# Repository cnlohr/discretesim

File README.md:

# (work in progress) Dumb as a Box of Rocks SPICE Simulation

goals:
1. as simple as possible
2. linear runtime with circuit complexity.
3. support ultra complicated circuits.
4. be stable-by-default at the trade off of simulation speed.

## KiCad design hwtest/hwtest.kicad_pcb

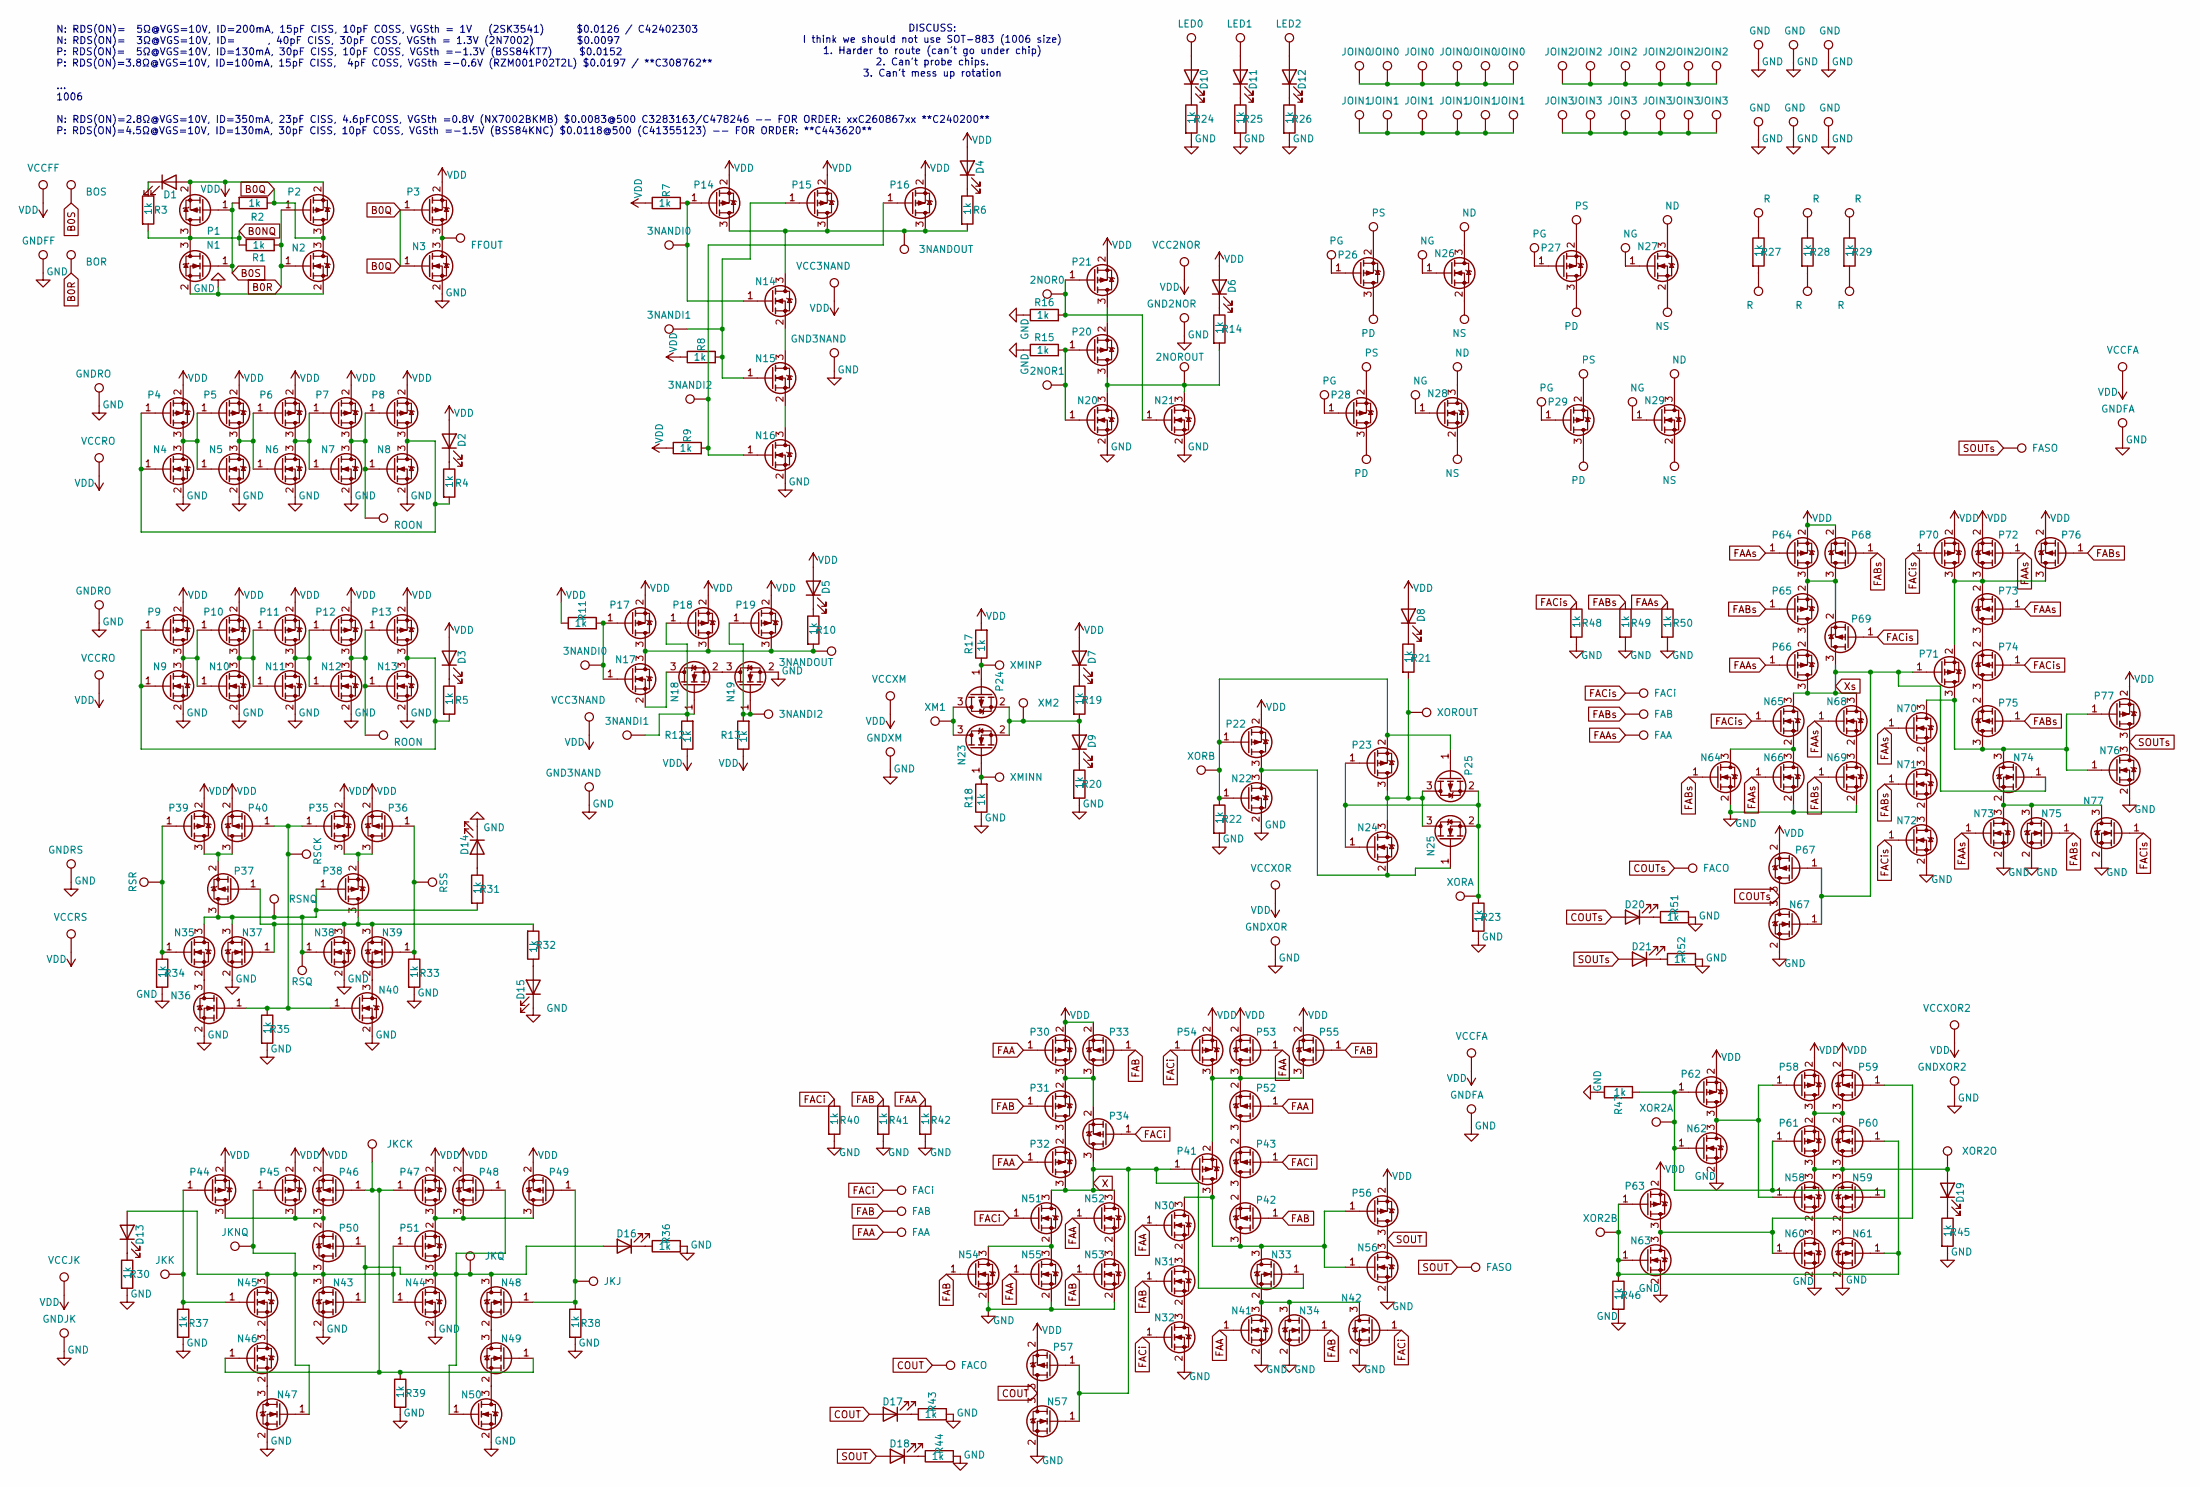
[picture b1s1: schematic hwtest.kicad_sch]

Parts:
D1, D2, D3, D4, D5, D6, D7, D8, D9, D10, D11, D12, D13, D14, D15, D16, D17, D18, D19, D20, D21: LED; LED_0402_1005Metric_COMPACT; LCSC C965793
N1, N2, N3, N4, N5, N6, N7, N8, N14, N15, N16, N20, N21, N22, N23, N24, N25, N26, N27, N30, N31, N32, N33, N34, N35, N36, N37, N38, N39, N40, N41, N42, N43, N44, N45, N46, N47, N48, N49, N50, N51, N52, N53, N54, N55, N56, N57, N58, N59, N60, N61, N62, N63: 2SK3541; SOT-723-COMPACT; LCSC C42402303
N9, N10, N11, N12, N13, N17, N18, N19, N28, N29: NX7002BKMB315; DFN1006-3-NCH; LCSC C240200
N64, N65, N66, N67, N68, N69, N70, N71, N72, N73, N74, N75, N76, N77: 2SK3541; DFN1006-3-NCH; LCSC C240200
P1, P2, P3, P4, P5, P6, P7, P8, P14, P15, P16, P20, P21, P22, P23, P24, P25, P26, P27, P30, P31, P32, P33, P34, P35, P36, P37, P38, P39, P40, P41, P42, P43, P44, P45, P46, P47, P48, P49, P50, P51, P52, P53, P54, P55, P56, P57, P58, P59, P60, P61, P62, P63: RZM001P02T2L; SOT-723-COMPACTP; LCSC C308762
P9, P10, P11, P12, P13, P17, P18, P19, P28, P29: BSS84KNC; DFN1006-3-PCH; LCSC C443620
P64, P65, P66, P67, P68, P69, P70, P71, P72, P73, P74, P75, P76, P77: RZM001P02T2L; DFN1006-3-PCH; LCSC C443620
R1, R2, R3, R4, R5, R6, R7, R8, R9, R10, R11, R12, R13, R14, R15, R16, R17, R18, R19, R20, R21, R22, R23, R24, R25, R26, R27, R28, R29, R30, R31, R32, R33, R34, R35, R36, R37, R38, R39, R40, R41, R42, R43, R44, R45, R46, R47, R48, R49, R50, R51, R52: 1k; R_0402_1005Metric_COMPACT; LCSC C11702
TP1: BOS; TPTHRU; LCSC C25503131
TP2: BOR; TPTHRU; LCSC C25503131
TP3: FFOUT; TPTHRU; LCSC C25503131
TP4, TP11: ROON; TPTHRU; LCSC C25503131
TP5: VCCFF; TPTHRU; LCSC C25503131
TP6: GNDFF; TPTHRU; LCSC C25503131
TP7, TP9: GNDRO; TPTHRU; LCSC C25503131
TP8, TP10: VCCRO; TPTHRU; LCSC C25503131
TP12, TP21: 3NANDOUT; TPTHRU; LCSC C25503131
TP13, TP19: 3NANDI0; TPTHRU; LCSC C25503131
TP14, TP18: 3NANDI1; TPTHRU; LCSC C25503131
TP15, TP20: 3NANDI2; TPTHRU; LCSC C25503131
TP16, TP22: VCC3NAND; TPTHRU; LCSC C25503131
TP17, TP23: GND3NAND; TPTHRU; LCSC C25503131
TP24: 2NOR1; TPTHRU; LCSC C25503131
TP25: 2NOR0; TPTHRU; LCSC C25503131
TP26: 2NOROUT; TPTHRU; LCSC C25503131
TP27: VCC2NOR; TPTHRU; LCSC C25503131
TP28: GND2NOR; TPTHRU; LCSC C25503131
TP29: XORB; TPTHRU; LCSC C25503131
TP30: XM1; TPTHRU; LCSC C25503131
TP31: XM2; TPTHRU; LCSC C25503131
TP32: XMINP; TPTHRU; LCSC C25503131
TP33: XMINN; TPTHRU; LCSC C25503131
TP34: XORA; TPTHRU; LCSC C25503131
TP35: VCCXM; TPTHRU; LCSC C25503131
TP36: GNDXM; TPTHRU; LCSC C25503131
TP37: XOROUT; TPTHRU; LCSC C25503131
TP38: VCCXOR; TPTHRU; LCSC C25503131
TP39: GNDXOR; TPTHRU; LCSC C25503131
TP40: LED0; TPTHRU; LCSC C25503131
TP41: LED1; TPTHRU; LCSC C25503131
TP42: LED2; TPTHRU; LCSC C25503131
TP43, TP68, TP74, TP80: PS; TPTHRU; LCSC C25503131
TP44, TP67, TP73, TP79: PG; TPTHRU; LCSC C25503131
TP45, TP69, TP75, TP81: PD; TPTHRU; LCSC C25503131
TP46, TP71, TP77, TP83: ND; TPTHRU; LCSC C25503131
TP47, TP72, TP78, TP84: NS; TPTHRU; LCSC C25503131
TP48, TP70, TP76, TP82: NG; TPTHRU; LCSC C25503131
TP49, TP50, TP51, TP52, TP53, TP54: R; TPTHRU; LCSC C25503131
TP55, TP56, TP57, TP58, TP59, TP60: JOIN0; TPTHRU; LCSC C25503131
TP61, TP62, TP63, TP64, TP65, TP66: JOIN1; TPTHRU; LCSC C25503131
TP85, TP86, TP87, TP88, TP89, TP90: JOIN2; TPTHRU; LCSC C25503131
TP91, TP92, TP93, TP94, TP95, TP96: JOIN3; TPTHRU; LCSC C25503131
TP97, TP98, TP99, TP100, TP101, TP102: GND; TPTHRU; LCSC C25503131
TP103: JKCK; TPTHRU; LCSC C25503131
TP104: JKQ; TPTHRU; LCSC C25503131
TP105: JKNQ; TPTHRU; LCSC C25503131
TP106: RSNQ; TPTHRU; LCSC C25503131
TP107: RSQ; TPTHRU; LCSC C25503131
TP108: RSR; TPTHRU; LCSC C25503131
TP109: RSS; TPTHRU; LCSC C25503131
TP110: RSCK; TPTHRU; LCSC C25503131
TP111: GNDRS; TPTHRU; LCSC C25503131
TP112: VCCRS; TPTHRU; LCSC C25503131
TP113: JKK; TPTHRU; LCSC C25503131
TP114: JKJ; TPTHRU; LCSC C25503131
TP115: VCCJK; TPTHRU; LCSC C25503131
TP116: GNDJK; TPTHRU; LCSC C25503131
TP117, TP132: FACO; TPTHRU; LCSC C25503131
TP118, TP133: FASO; TPTHRU; LCSC C25503131
TP119, TP129: FACi; TPTHRU; LCSC C25503131
TP120, TP130: FAB; TPTHRU; LCSC C25503131
TP121, TP131: FAA; TPTHRU; LCSC C25503131
TP122, TP134: VCCFA; TPTHRU; LCSC C25503131
TP123, TP135: GNDFA; TPTHRU; LCSC C25503131
TP124: XOR2A; TPTHRU; LCSC C25503131
TP125: XOR2B; TPTHRU; LCSC C25503131
TP126: XOR2O; TPTHRU; LCSC C25503131
TP127: VCCXOR2; TPTHRU; LCSC C25503131
TP128: GNDXOR2; TPTHRU; LCSC C25503131

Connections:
B0NQ: N1.3 (D), P1.3 (D), R1.1, R3.2
B0Q: N2.3 (D), N3.1 (G), P2.3 (D), P3.1 (G), R2.1
B0R: N2.1 (G), P2.1 (G), R1.2, TP2.1
B0S: N1.1 (G), P1.1 (G), R2.2, TP1.1
COUT: D17.2 (A), N57.3 (D), P57.3 (D), TP117.1
COUTs: D20.2 (A), N67.3 (D), P67.3 (D), TP132.1
FAA: N30.1 (G), N41.1 (G), N52.1 (G), N55.1 (G), P30.1 (G), P32.1 (G), P52.1 (G), P53.1 (G), R42.1, TP121.1
FAAs: N66.1 (G), N68.1 (G), N70.1 (G), N73.1 (G), P64.1 (G), P66.1 (G), P72.1 (G), P73.1 (G), R50.1, TP131.1
FAB: N31.1 (G), N34.1 (G), N53.1 (G), N54.1 (G), P31.1 (G), P33.1 (G), P42.1 (G), P55.1 (G), R41.1, TP120.1
FABs: N64.1 (G), N69.1 (G), N71.1 (G), N75.1 (G), P65.1 (G), P68.1 (G), P75.1 (G), P76.1 (G), R49.1, TP130.1
FACi: N32.1 (G), N42.1 (G), N51.1 (G), P34.1 (G), P43.1 (G), P54.1 (G), R40.1, TP119.1
FACis: N65.1 (G), N72.1 (G), N77.1 (G), P69.1 (G), P70.1 (G), P74.1 (G), R48.1, TP129.1
GND: D14.1 (K), D15.1 (K), N1.2 (S), N2.2 (S), N3.2 (S), N4.2 (S), N5.2 (S), N6.2 (S), N7.2 (S), N8.2 (S), N9.2 (S), N10.2 (S), N11.2 (S), N12.2 (S), N13.2 (S), N16.2 (S), N19.2 (S), N20.2 (S), N21.2 (S), N22.2 (S), N32.2 (S), N34.2 (S), N36.2 (S), N37.2 (S), N38.2 (S), N40.2 (S), N41.2 (S), N42.2 (S), N43.2 (S), N44.2 (S), N47.2 (S), N50.2 (S), N53.2 (S), N54.2 (S), N55.2 (S), N56.2 (S), N57.2 (S), N60.2 (S), N61.2 (S), N62.2 (S), N63.2 (S), N64.2 (S), N66.2 (S), N67.2 (S), N69.2 (S), N72.2 (S), N73.2 (S), N75.2 (S), N76.2 (S), N77.2 (S), R15.1, R16.1, R18.1, R20.2, R22.2, R23.2, R24.2, R25.2, R26.2, R30.2, R33.2, R34.2, R35.2, R36.2, R37.2, R38.2, R39.2, R40.2, R41.2, R42.2, R43.2, R44.2, R45.2, R46.2, R47.2, R48.2, R49.2, R50.2, R51.2, R52.2, TP6.1, TP7.1, TP9.1, TP17.1, TP23.1, TP28.1, TP36.1, TP39.1, TP97.1, TP98.1, TP99.1, TP100.1, TP101.1, TP102.1, TP111.1, TP116.1, TP123.1, TP128.1, TP135.1
unnamed: D1.1 (K), R3.1
unnamed: D2.1 (K), R4.1
unnamed: D3.1 (K), R5.1
unnamed: D4.1 (K), R6.1
unnamed: D5.1 (K), R10.1
unnamed: D6.1 (K), R14.1
unnamed: D7.1 (K), R19.1
unnamed: D8.1 (K), R21.1
unnamed: D9.2 (A), N23.2 (S), P24.2 (S), R19.2, TP31.1
unnamed: D9.1 (K), R20.1
unnamed: D10.2 (A), TP40.1
unnamed: D10.1 (K), R24.1
unnamed: D11.2 (A), TP41.1
unnamed: D11.1 (K), R25.1
unnamed: D12.2 (A), TP42.1
unnamed: D12.1 (K), R26.1
unnamed: D13.2 (A), N43.3 (D), N44.1 (G), N45.3 (D), N47.1 (G), P45.1 (G), P50.3 (D), P51.1 (G), TP105.1
unnamed: D13.1 (K), R30.1
unnamed: D14.2 (A), R31.1
unnamed: D15.2 (A), R32.1
unnamed: D16.2 (A), N43.1 (G), N44.3 (D), N48.3 (D), N50.1 (G), P48.1 (G), P50.1 (G), P51.3 (D), TP104.1
unnamed: D16.1 (K), R36.1
unnamed: D17.1 (K), R43.1
unnamed: D18.1 (K), R44.1
unnamed: D19.2 (A), N58.3 (D), N59.3 (D), P60.3 (D), P61.3 (D), TP126.1
unnamed: D19.1 (K), R45.1
unnamed: D20.1 (K), R51.1
unnamed: D21.1 (K), R52.1
unnamed: N3.3 (D), P3.3 (D), TP3.1
unnamed: N4.3 (D), N5.1 (G), P4.3 (D), P5.1 (G)
unnamed: N4.1 (G), N8.3 (D), P4.1 (G), P8.3 (D), R4.2
unnamed: N5.3 (D), N6.1 (G), P5.3 (D), P6.1 (G)
unnamed: N6.3 (D), N7.1 (G), P6.3 (D), P7.1 (G)
unnamed: N7.3 (D), N8.1 (G), P7.3 (D), P8.1 (G), TP4.1
unnamed: N10.3 (D), N11.1 (G), P10.3 (D), P11.1 (G)
unnamed: N9.3 (D), N10.1 (G), P9.3 (D), P10.1 (G)
unnamed: N11.3 (D), N12.1 (G), P11.3 (D), P12.1 (G)
unnamed: N12.3 (D), N13.1 (G), P12.3 (D), P13.1 (G), TP11.1
unnamed: N9.1 (G), N13.3 (D), P9.1 (G), P13.3 (D), R5.2
unnamed: N14.3 (D), P14.3 (D), P15.3 (D), P16.3 (D), R6.2, TP12.1
unnamed: N14.1 (G), P14.1 (G), R7.2, TP13.1
unnamed: N14.2 (S), N15.3 (D)
unnamed: N15.1 (G), P15.1 (G), R8.2, TP14.1
unnamed: N15.2 (S), N16.3 (D)
unnamed: N16.1 (G), P16.1 (G), R9.2, TP15.1
unnamed: N17.3 (D), P17.3 (D), P18.3 (D), P19.3 (D), R10.2, TP21.1
unnamed: N17.1 (G), P17.1 (G), R11.2, TP19.1
unnamed: N17.2 (S), N18.3 (D)
unnamed: N18.1 (G), P18.1 (G), R12.2, TP18.1
unnamed: N18.2 (S), N19.3 (D)
unnamed: N19.1 (G), P19.1 (G), R13.2, TP20.1
unnamed: N20.3 (D), N21.3 (D), P20.3 (D), R14.2, TP26.1
unnamed: N20.1 (G), P20.1 (G), R15.2, TP24.1
unnamed: N21.1 (G), P21.1 (G), R16.2, TP25.1
unnamed: N22.3 (D), N24.2 (S), N25.1 (G), P22.3 (D)
unnamed: N22.1 (G), P22.1 (G), P23.2 (S), P25.1 (G), R22.1, TP29.1
unnamed: N23.3 (D), P24.3 (D), TP30.1
unnamed: N23.1 (G), R18.2, TP33.1
unnamed: N24.3 (D), N25.3 (D), P23.3 (D), P25.3 (D), R21.2, TP37.1
unnamed: N24.1 (G), N25.2 (S), P23.1 (G), P25.2 (S), R23.1, TP34.1
unnamed: N26.3 (D), TP46.1
unnamed: N26.1 (G), TP48.1
unnamed: N26.2 (S), TP47.1
unnamed: N27.3 (D), TP71.1
unnamed: N27.1 (G), TP70.1
unnamed: N27.2 (S), TP72.1
unnamed: N28.3 (D), TP77.1
unnamed: N28.1 (G), TP76.1
unnamed: N28.2 (S), TP78.1
unnamed: N29.3 (D), TP83.1
unnamed: N29.1 (G), TP82.1
unnamed: N29.2 (S), TP84.1
unnamed: N30.3 (D), N33.3 (D), N56.1 (G), P41.3 (D), P42.3 (D), P56.1 (G)
unnamed: N30.2 (S), N31.3 (D)
unnamed: N31.2 (S), N32.3 (D)
unnamed: N33.2 (S), N34.3 (D), N41.3 (D), N42.3 (D)
unnamed: N35.3 (D), N37.3 (D), N38.1 (G), P37.3 (D), P38.1 (G), R31.2, TP106.1, TP107.1
unnamed: N35.1 (G), P39.1 (G), R34.1, TP108.1
unnamed: N35.2 (S), N36.3 (D)
unnamed: N36.1 (G), N40.1 (G), P35.1 (G), P40.1 (G), R35.1, TP110.1
unnamed: N37.1 (G), N38.3 (D), N39.3 (D), P37.1 (G), P38.3 (D), R32.2
unnamed: N39.1 (G), P36.1 (G), R33.1, TP109.1
unnamed: N39.2 (S), N40.3 (D)
unnamed: N45.1 (G), P44.1 (G), R37.1, TP113.1
unnamed: N45.2 (S), N46.3 (D)
unnamed: N46.1 (G), N49.1 (G), P46.1 (G), P47.1 (G), R39.1, TP103.1
unnamed: N46.2 (S), N47.3 (D)
unnamed: N48.1 (G), P49.1 (G), R38.1, TP114.1
unnamed: N48.2 (S), N49.3 (D)
unnamed: N49.2 (S), N50.3 (D)
unnamed: N51.2 (S), N54.3 (D), N55.3 (D)
unnamed: N52.2 (S), N53.3 (D)
unnamed: N58.1 (G), N62.3 (D), P58.1 (G), P62.3 (D)
unnamed: N58.2 (S), N60.3 (D)
unnamed: N59.1 (G), N62.1 (G), P61.1 (G), P62.1 (G), R47.1, TP124.1
unnamed: N59.2 (S), N61.3 (D)
unnamed: N60.1 (G), N63.3 (D), P59.1 (G), P63.3 (D)
unnamed: N61.1 (G), N63.1 (G), P60.1 (G), P63.1 (G), R46.1, TP125.1
unnamed: N64.3 (D), N65.2 (S), N66.3 (D)
unnamed: N68.2 (S), N69.3 (D)
unnamed: N70.3 (D), N74.3 (D), N76.1 (G), P71.3 (D), P75.3 (D), P77.1 (G)
unnamed: N70.2 (S), N71.3 (D)
unnamed: N71.2 (S), N72.3 (D)
unnamed: N73.3 (D), N74.2 (S), N75.3 (D), N77.3 (D)
unnamed: P20.2 (S), P21.3 (D)
unnamed: P24.1 (G), R17.1, TP32.1
unnamed: P26.3 (D), TP45.1
unnamed: P26.1 (G), TP44.1
unnamed: P26.2 (S), TP43.1
unnamed: P27.3 (D), TP69.1
unnamed: P27.1 (G), TP67.1
unnamed: P27.2 (S), TP68.1
unnamed: P28.3 (D), TP75.1
unnamed: P28.1 (G), TP73.1
unnamed: P28.2 (S), TP74.1
unnamed: P29.3 (D), TP81.1
unnamed: P29.1 (G), TP79.1
unnamed: P29.2 (S), TP80.1
unnamed: P30.3 (D), P31.2 (S), P33.3 (D), P34.2 (S)
unnamed: P31.3 (D), P32.2 (S)
unnamed: P35.3 (D), P36.3 (D), P38.2 (S)
unnamed: P37.2 (S), P39.3 (D), P40.3 (D)
unnamed: P41.2 (S), P52.2 (S), P53.3 (D), P54.3 (D), P55.3 (D)
unnamed: P42.2 (S), P43.3 (D)
unnamed: P43.2 (S), P52.3 (D)
unnamed: P44.3 (D), P45.3 (D), P46.3 (D), P50.2 (S)
unnamed: P47.3 (D), P48.3 (D), P49.3 (D), P51.2 (S)
unnamed: P58.3 (D), P59.3 (D), P60.2 (S), P61.2 (S)
unnamed: P64.3 (D), P65.2 (S), P68.3 (D), P69.2 (S)
unnamed: P65.3 (D), P66.2 (S)
unnamed: P70.3 (D), P71.2 (S), P72.3 (D), P73.2 (S), P76.3 (D)
unnamed: P73.3 (D), P74.2 (S)
unnamed: P74.3 (D), P75.2 (S)
unnamed: R27.1, TP49.1
unnamed: R27.2, TP50.1
unnamed: R28.1, TP51.1
unnamed: R28.2, TP52.1
unnamed: R29.1, TP53.1
unnamed: R29.2, TP54.1
unnamed: TP55.1, TP56.1, TP57.1, TP58.1, TP59.1, TP60.1
unnamed: TP61.1, TP62.1, TP63.1, TP64.1, TP65.1, TP66.1
unnamed: TP85.1, TP86.1, TP87.1, TP88.1, TP89.1, TP90.1
unnamed: TP91.1, TP92.1, TP93.1, TP94.1, TP95.1, TP96.1
SOUT: D18.2 (A), N56.3 (D), P56.3 (D), TP118.1
SOUTs: D21.2 (A), N76.3 (D), P77.3 (D), TP133.1
VDD: D1.2 (A), D2.2 (A), D3.2 (A), D4.2 (A), D5.2 (A), D6.2 (A), D7.2 (A), D8.2 (A), P1.2 (S), P2.2 (S), P3.2 (S), P4.2 (S), P5.2 (S), P6.2 (S), P7.2 (S), P8.2 (S), P9.2 (S), P10.2 (S), P11.2 (S), P12.2 (S), P13.2 (S), P14.2 (S), P15.2 (S), P16.2 (S), P17.2 (S), P18.2 (S), P19.2 (S), P21.2 (S), P22.2 (S), P30.2 (S), P33.2 (S), P35.2 (S), P36.2 (S), P39.2 (S), P40.2 (S), P44.2 (S), P45.2 (S), P46.2 (S), P47.2 (S), P48.2 (S), P49.2 (S), P53.2 (S), P54.2 (S), P55.2 (S), P56.2 (S), P57.2 (S), P58.2 (S), P59.2 (S), P62.2 (S), P63.2 (S), P64.2 (S), P67.2 (S), P68.2 (S), P70.2 (S), P72.2 (S), P76.2 (S), P77.2 (S), R7.1, R8.1, R9.1, R11.1, R12.1, R13.1, R17.2, TP5.1, TP8.1, TP10.1, TP16.1, TP22.1, TP27.1, TP35.1, TP38.1, TP112.1, TP115.1, TP122.1, TP127.1, TP134.1
X: N33.1 (G), N51.3 (D), N52.3 (D), N57.1 (G), P32.3 (D), P34.3 (D), P41.1 (G), P57.1 (G)
Xs: N65.3 (D), N67.1 (G), N68.3 (D), N74.1 (G), P66.3 (D), P67.1 (G), P69.3 (D), P71.1 (G)

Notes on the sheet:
DISCUSS: I think we should not use SOT-883 (1006 size) 1. Harder to route (can't go under chip) 2. Can't probe chips. 3. Can't mess up rotation
N: RDS(ON)= 5Ω@VGS=10V, ID=200mA, 15pF CISS, 10pF COSS, VGSth = 1V (2SK3541) $0.0126 / C42402303 N: RDS(ON)= 3Ω@VGS=10V, ID= , 40pF CISS, 30pF COSS, VGSth = 1.3V (2N7002) $0.0097 P: RDS(ON)= 5Ω@VGS=10V, ID=130mA, 30pF CISS, 10pF COSS, VGSth =-1.3V (BSS84KT7) $0.0152 P: RDS(ON)=3.8Ω@VGS=10V, ID=100m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

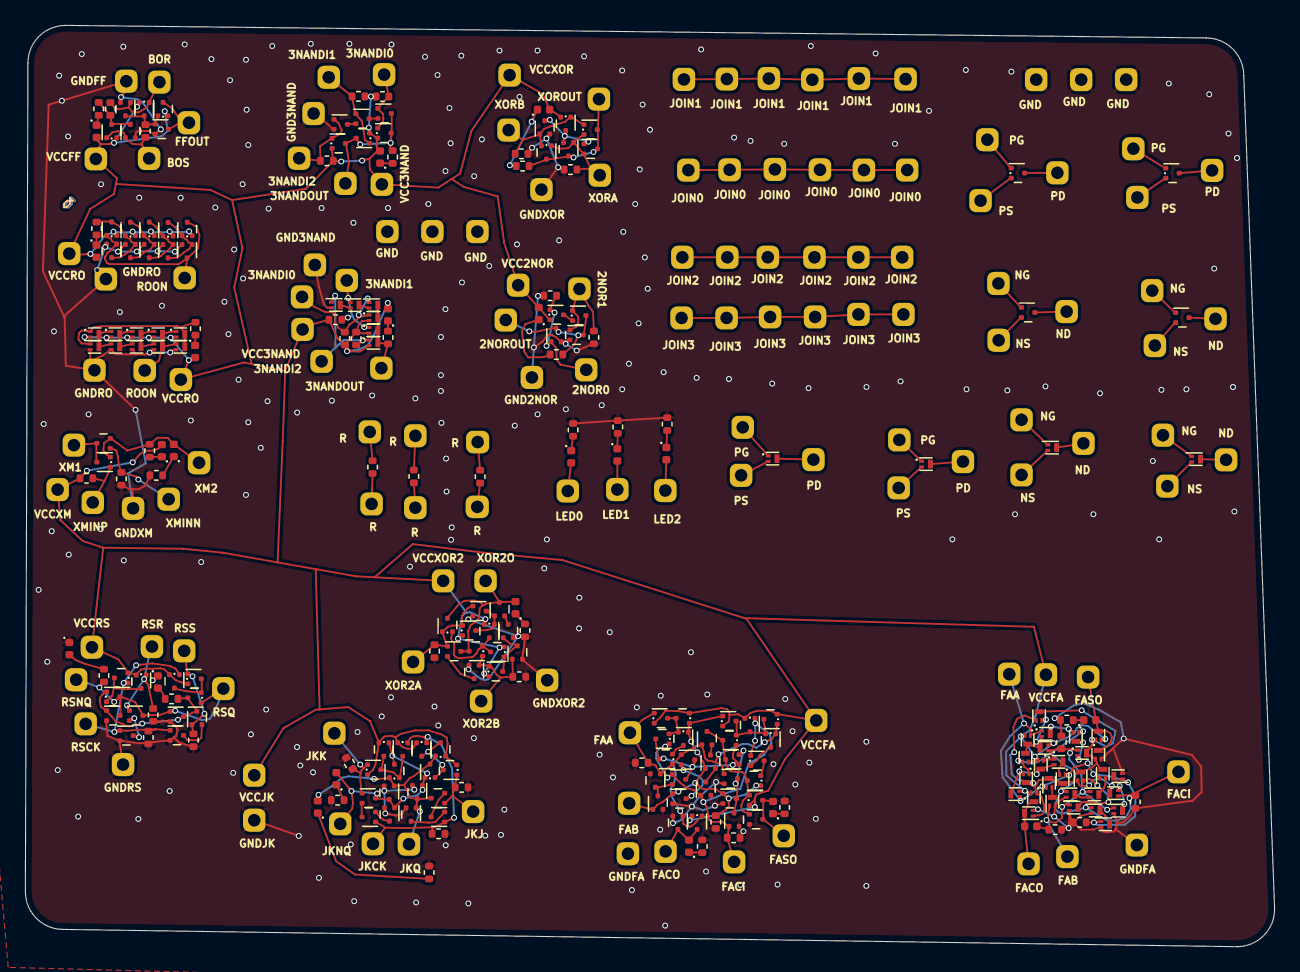
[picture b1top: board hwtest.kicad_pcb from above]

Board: 2 copper layers, 99.7 x 73.5 mm, 362 parts (0 on the bottom side), 161 nets.

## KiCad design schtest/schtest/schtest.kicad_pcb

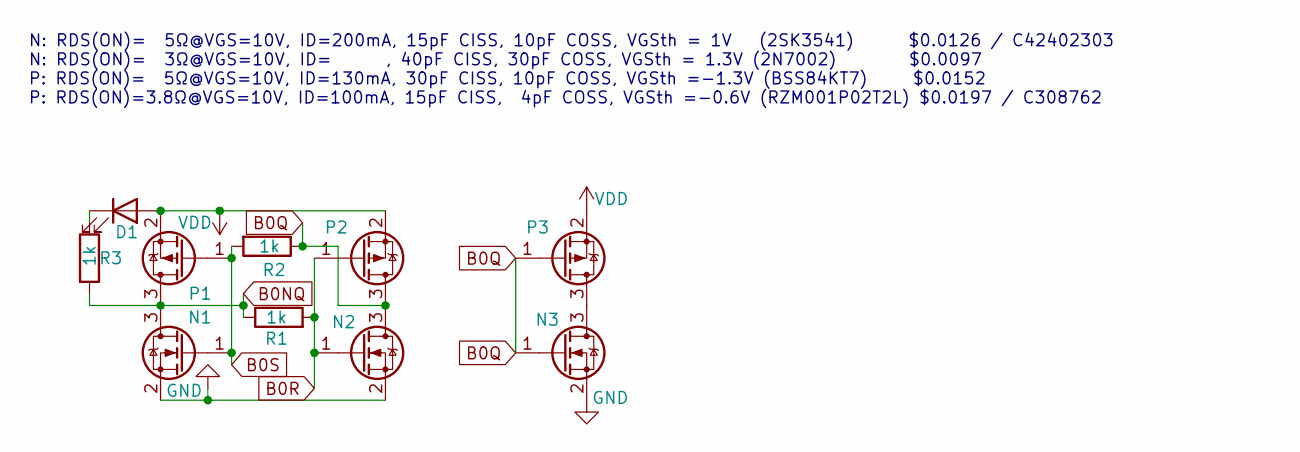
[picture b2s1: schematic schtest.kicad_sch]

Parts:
D1: LED; LED_0402_1005Metric_COMPACT; LCSC C965793
N1, N2, N3: 2SK3541; SOT-723-COMPACT; LCSC C42402303
P1, P2, P3: RZM001P02T2L; SOT-723-COMPACTP; LCSC C308762
R1, R2, R3: 1k; R_0402_1005Metric_COMPACT; LCSC C11702

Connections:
B0NQ: N1.3 (D), P1.3 (D), R1.1, R3.2
B0Q: N2.3 (D), N3.1 (G), P2.3 (D), P3.1 (G), R2.1
B0R: N2.1 (G), P2.1 (G), R1.2
B0S: N1.1 (G), P1.1 (G), R2.2
GND: N1.2 (S), N2.2 (S), N3.2 (S)
unnamed: D1.1 (K), R3.1
unnamed: N3.3 (D), P3.3 (D)
VDD: D1.2 (A), P1.2 (S), P2.2 (S), P3.2 (S)

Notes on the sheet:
N: RDS(ON)= 5Ω@VGS=10V, ID=200mA, 15pF CISS, 10pF COSS, VGSth = 1V (2SK3541) $0.0126 / C42402303 N: RDS(ON)= 3Ω@VGS=10V, ID= , 40pF CISS, 30pF COSS, VGSth = 1.3V (2N7002) $0.0097 P: RDS(ON)= 5Ω@VGS=10V, ID=130mA, 30pF CISS, 10pF COSS, VGSth =-1.3V (BSS84KT7) $0.0152 P: RDS(ON)=3.8Ω@VGS=10V, ID=100m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

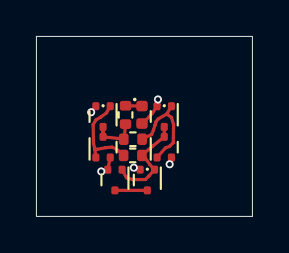
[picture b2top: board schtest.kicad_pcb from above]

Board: 4 copper layers, 12.0 x 10.0 mm, 10 parts (0 on the bottom side), 8 nets.

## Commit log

2025-02-02 Tinkering with yspice
2025-02-02 Cleanup schematic
2025-02-02 Bump designs
2025-02-02 Update design
2025-02-02 Bump
2025-02-02 Add emu basic
2025-02-08 Thinking through a simulation solution
2025-02-11 Toying with combo test
2025-02-12 Bump combotest
2025-02-13 semi still not quite working.
2025-02-13 Working fet
2025-06-23 Poking around
2025-06-25 Add schtest2
2025-06-25 Forgot the wbk
2025-06-25 Playing with an hw test
2025-06-26 Tweak design.
2025-06-26 bump for order version
2025-06-28 Tweak test
2025-06-29 Add note about alternate full adders
2025-07-11 Looking at another sim
2025-12-20 playing with another way of working
2025-12-20 Coming laong
2025-12-21 Getting closer
2025-12-21 Move files around
2025-12-21 Update showing functional sim
2025-12-21 Add more tests
2025-12-21 More wacky circuits
2025-12-22 Add capacitors
2025-12-22 forgot test circuit
2025-12-22 Add a divider example
2025-12-22 Working copy
2025-12-22 add note about inductor
2025-12-25 Add rc time constant test
